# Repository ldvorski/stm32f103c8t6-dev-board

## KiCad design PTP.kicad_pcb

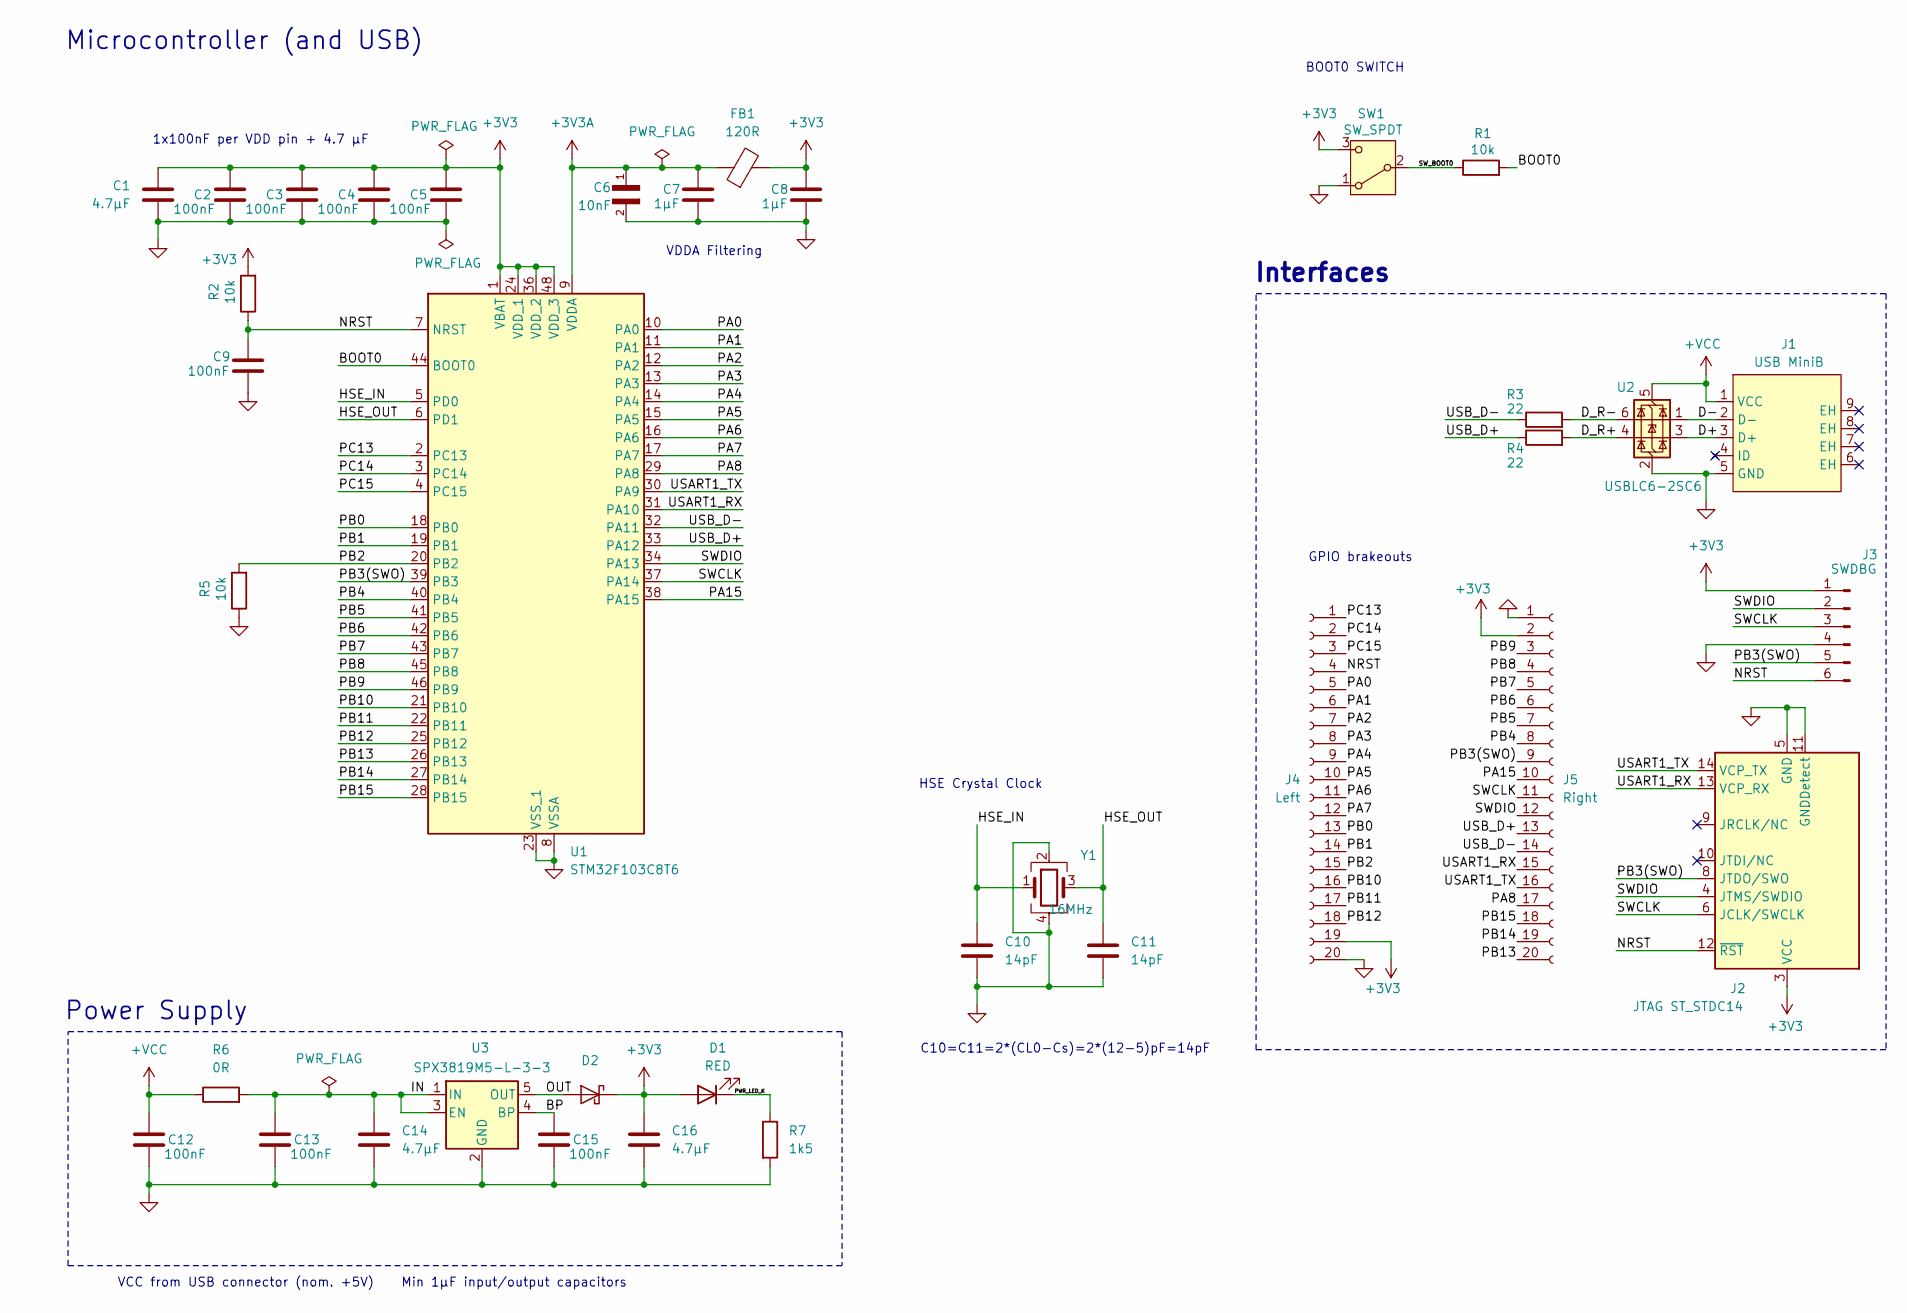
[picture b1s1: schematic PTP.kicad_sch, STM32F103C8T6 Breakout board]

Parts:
C1, C14, C16: 4.7µF; R_0805_2012Metric; JLCPCB P# C1746
C2, C3, C4, C5, C9, C12, C13, C15: 100nF; C_0402_1005Metric; JLCPCB P# C1525
C6: 10nF; C_0402_1005Metric; JLCPCB P# C1524
C7, C8: 1µF; C_0603_1608Metric; JLCPCB P# C1592
C10, C11: 14pF; C_0402_1005Metric; JLCPCB P# C458857
D1: RED; LED_1206_3216Metric; JLCPCB P# C49018
D2: RB161VA-20TR; D_SOD-323; JLCPCB P# C308724
FB1: 120R; R_0805_2012Metric; JLCPCB P# C5671
J1: USB MiniB; KH-MINI-SMT-5P-Cu; JLCPCB P# C2688795
J2: JTAG ST_STDC14; FTSH-107-01-L-DV-K; JLCPCB P# C5307809
J3: SWDBG; PinHeader_1x06_P2.54mm_Vertical
J4: Left; PinHeader_1x20_P2.54mm_Vertical
J5: Right; PinHeader_1x20_P2.54mm_Vertical
R1, R2, R5: 10k; R_0603_1608Metric; JLCPCB P# C188363
R3, R4: 22; R_0603_1608Metric; JLCPCB P# C1203
R6: 0R; R_0805_2012Metric; JLCPCB P# C17477
R7: 1k5; R_0805_2012Metric; JLCPCB P# C4310
SW1: SW_SPDT; K3-1235S-F1; JLCPCB P# C92660
U1: STM32F103C8T6; LQFP-48_7x7mm_P0.5mm; JLCPCB P# C8734
U2: USBLC6-2SC6; SOT-23-6; JLCPCB P# C7519
U3: SPX3819M5-L-3-3; SOT-23-5; JLCPCB P# C20617301
Y1: 16MHz; Crystal_SMD_3225-4Pin_3.2x2.5mm; JLCPCB P# C12668

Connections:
+3V3: C1.1, C2.1, C3.1, C4.1, C5.1, C8.1, C16.1, D1.2 (A), D2.1 (K), FB1.2, J2.3 (VCC), J3.1, J4.19, J5.2, R2.2, SW1.3 (C), U1.1 (VBAT), U1.24 (VDD_1), U1.36 (VDD_2), U1.48 (VDD_3)
+3V3A: C6.1, C7.1, FB1.1, U1.9 (VDDA)
+VCC: C12.1, J1.1 (VCC), R6.1, U2.5 (VBUS)
/BOOT0: R1.2, U1.44 (BOOT0)
/BP: C15.1, U3.4 (BP)
/D+: J1.3 (D+), U2.3 (I/O2)
/D-: J1.2 (D-), U2.1 (I/O1)
/D_R+: R4.2, U2.4 (I/O2)
/D_R-: R3.2, U2.6 (I/O1)
/HSE_IN: C10.1, U1.5 (PD0), Y1.1
/HSE_OUT: C11.1, U1.6 (PD1), Y1.3
/IN: C13.1, C14.1, R6.2, U3.1 (IN), U3.3 (EN)
/NRST: C9.2, J2.12 (~RST), J3.6, J4.4, R2.1, U1.7 (NRST)
/OUT: D2.2 (A), U3.5 (OUT)
/PA0: J4.5, U1.10 (PA0)
/PA1: J4.6, U1.11 (PA1)
/PA2: J4.7, U1.12 (PA2)
/PA3: J4.8, U1.13 (PA3)
/PA4: J4.9, U1.14 (PA4)
/PA5: J4.10, U1.15 (PA5)
/PA6: J4.11, U1.16 (PA6)
/PA7: J4.12, U1.17 (PA7)
/PA8: J5.17, U1.29 (PA8)
/PA15: J5.10, U1.38 (PA15)
/PB0: J4.13, U1.18 (PB0)
/PB1: J4.14, U1.19 (PB1)
/PB2: J4.15, R5.2, U1.20 (PB2)
/PB3(SWO): J2.8 (JTDO/SWO), J3.5, J5.9, U1.39 (PB3)
/PB4: J5.8, U1.40 (PB4)
/PB5: J5.7, U1.41 (PB5)
/PB6: J5.6, U1.42 (PB6)
/PB7: J5.5, U1.43 (PB7)
/PB8: J5.4, U1.45 (PB8)
/PB9: J5.3, U1.46 (PB9)
/PB10: J4.16, U1.21 (PB10)
/PB11: J4.17, U1.22 (PB11)
/PB12: J4.18, U1.25 (PB12)
/PB13: J5.20, U1.26 (PB13)
/PB14: J5.19, U1.27 (PB14)
/PB15: J5.18, U1.28 (PB15)
/PC13: J4.1, U1.2 (PC13)
/PC14: J4.2, U1.3 (PC14)
/PC15: J4.3, U1.4 (PC15)
/PWR_LED_K: D1.1 (K), R7.1
/SWCLK: J2.6 (JCLK/SWCLK), J3.3, J5.11, U1.37 (PA14)
/SWDIO: J2.4 (JTMS/SWDIO), J3.2, J5.12, U1.34 (PA13)
/SW_BOOT0: R1.1, SW1.2 (B)
/USART1_RX: J2.13 (VCP_RX), J5.15, U1.31 (PA10)
/USART1_TX: J2.14 (VCP_TX), J5.16, U1.30 (PA9)
/USB_D+: J5.13, R4.1, U1.33 (PA12)
/USB_D-: J5.14, R3.1, U1.32 (PA11)
GND: C1.2, C2.2, C3.2, C4.2, C5.2, C6.2, C7.2, C8.2, C9.1, C10.2, C11.2, C12.2, C13.2, C14.2, C15.2, C16.2, J1.5 (GND), J2.5 (GND), J2.7 (GND), J2.11 (GNDDetect), J3.4, J4.20, J5.1, R5.1, R7.2, SW1.1 (A), U1.8 (VSSA), U1.23 (VSS_1), U1.35 (VSS_2), U1.47 (VSS_3), U2.2 (GND), U3.2 (GND), Y1.2, Y1.4

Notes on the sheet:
GPIO brakeouts
Microcontroller (and USB)
Power Supply
HSE Crystal Clock
1x100nF per VDD pin + 4.7 µF
VDDA Filtering
BOOT0 SWITCH
VCC from USB connector (nom. +5V) Min 1µF input/output capacitors
Interfaces
C10=C11=2*(CL0-Cs)=2*(12-5)pF=14pF

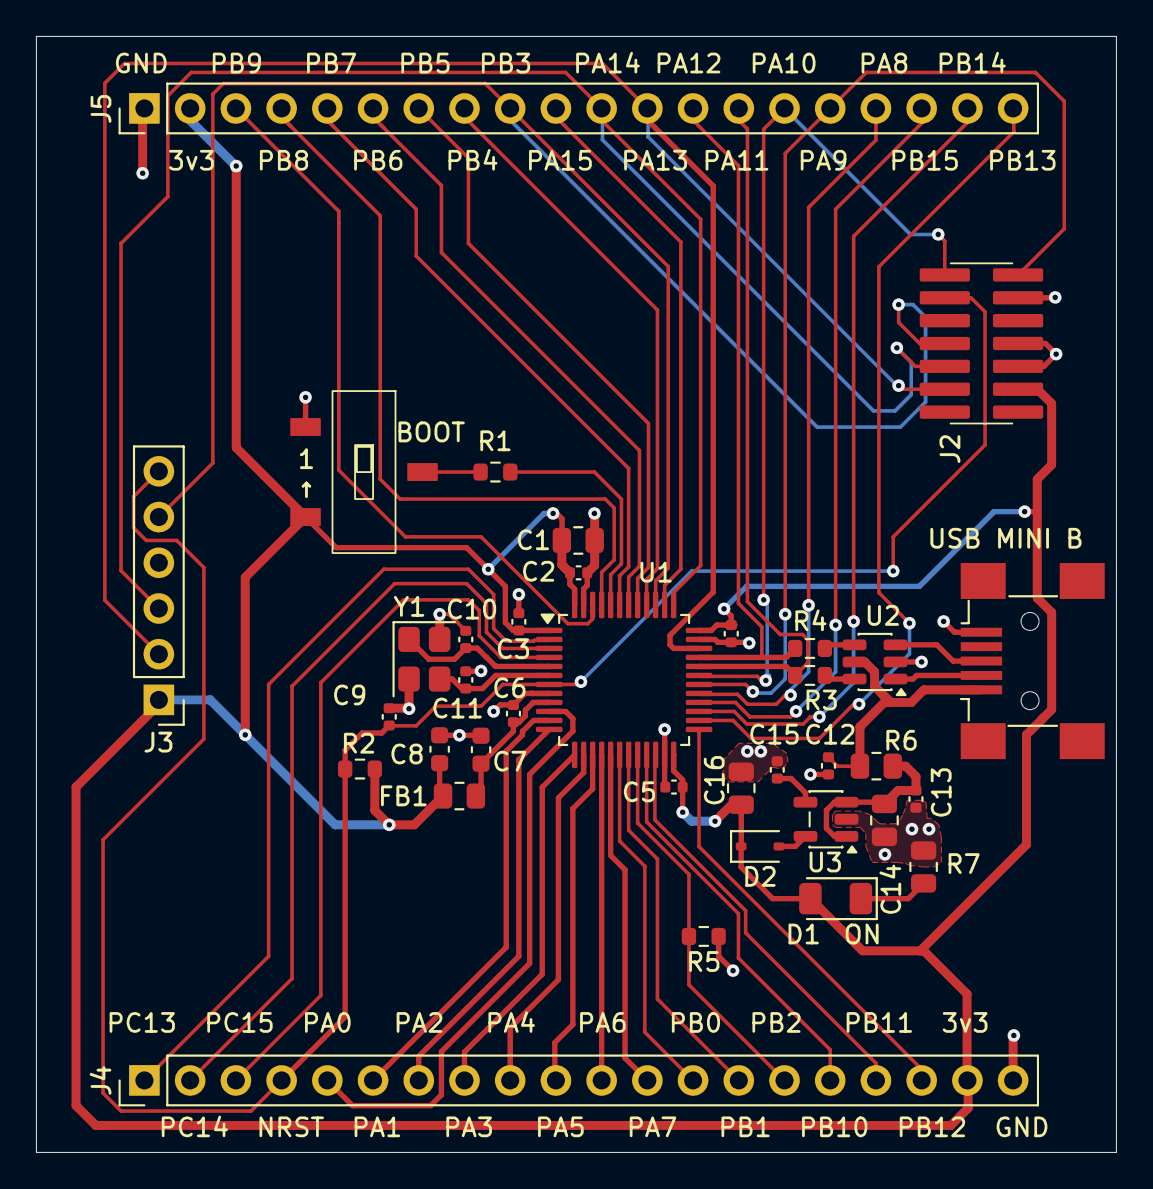
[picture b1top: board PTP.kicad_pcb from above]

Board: 2 copper layers, 60.0 x 62.0 mm, 36 parts (0 on the bottom side), 52 nets.

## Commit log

2025-11-11 v1.0 PTP project
2025-11-11 manufacturing names adjusted
2025-11-25 v1.1 PTP project - full GPIO breakout, STDC14 port for stlinkv3minie programming
